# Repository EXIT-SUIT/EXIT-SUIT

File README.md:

# EXIT SUIT
 
The EXIT SUIT is a full-body force-feedback navigation and performance suit for Virtual Reality. This repo contains our code so far for connecting the EXIT SUIT to Unity. 

We are building a community of supporters to help us bring the EXIT SUIT to the public. We recognise it is an important step in the development of human/computer interface and virtual reality.   
<br/><br/> 
   
<br/><br/>
# Community  
 
* Youtube: https://www.youtube.com/@WillieWinkler

* Instagram: https://www.instagram.com/exitsuit/

* Patreon: https://www.patreon.com/EXITSUIT

* Discord: https://discord.gg/Rf7WjFDc

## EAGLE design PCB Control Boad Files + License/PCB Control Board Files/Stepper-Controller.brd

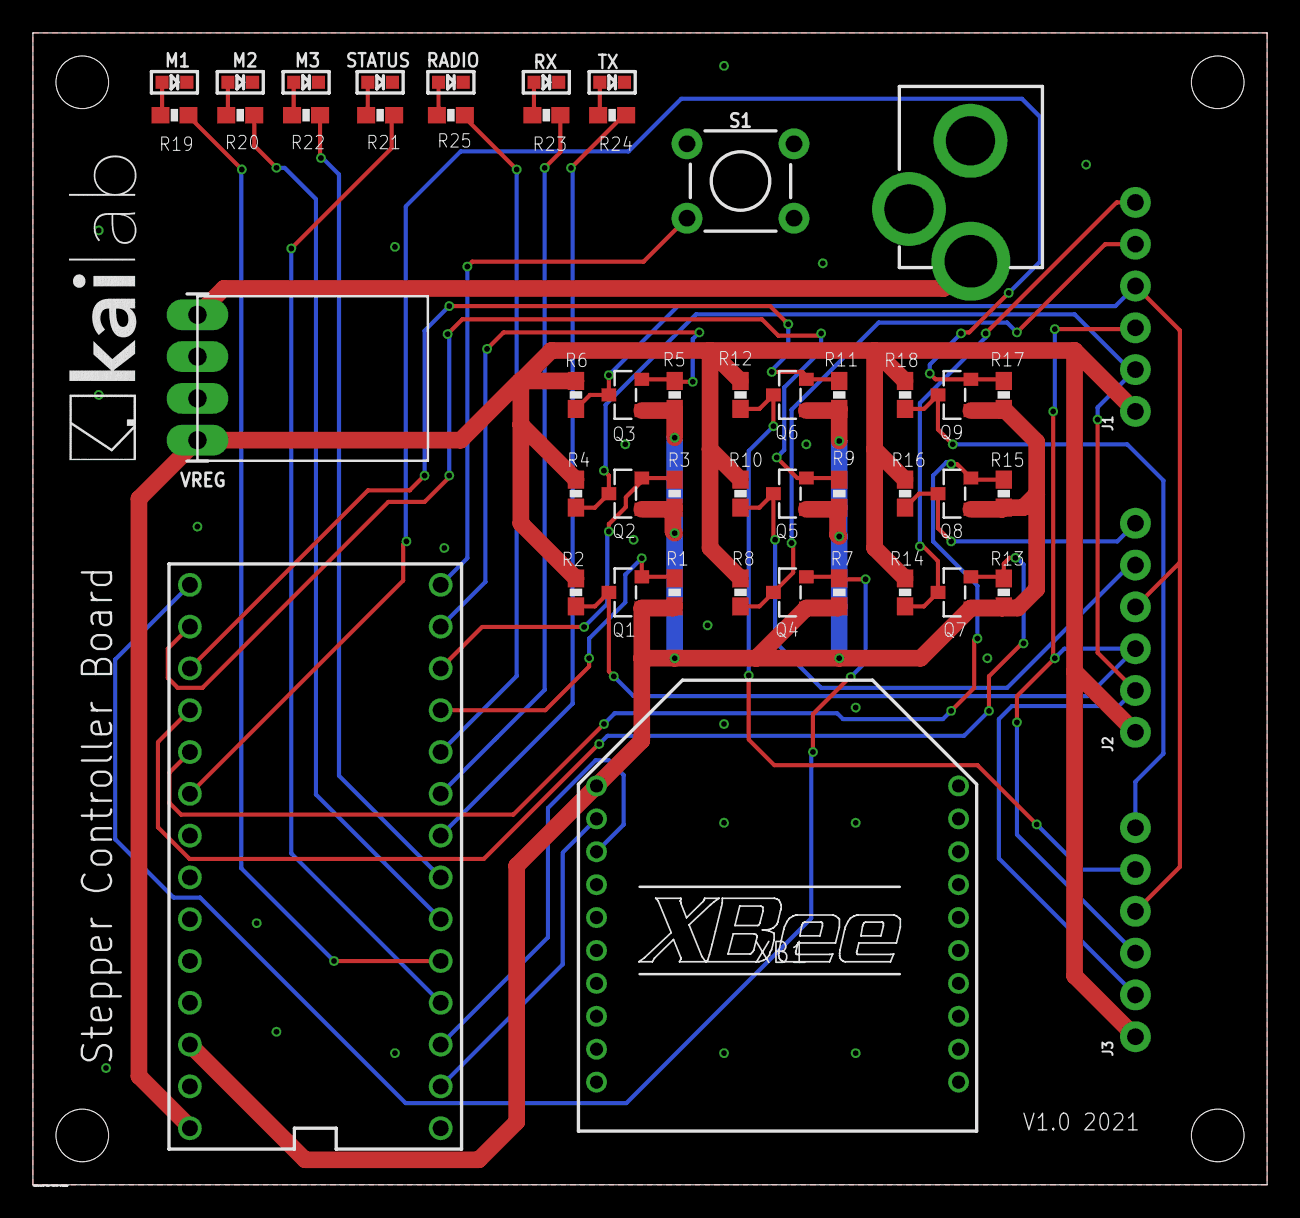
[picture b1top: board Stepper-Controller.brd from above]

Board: 2 copper layers, 75.0 x 70.0 mm, 49 parts (0 on the bottom side), 39 nets.

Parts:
J1, J2, J3: 1X06_NO_SILK
J4: POWER_JACKPTH_LOCK; POWER_JACK_PTH_LOCK
M1, M2, M3: MICROBUILDER_CHIPLED_0603
Q1, Q2, Q3, Q4, Q5, Q6, Q7, Q8, Q9: BSS138; SOT23
R1, R2, R3, R4, R5, R6, R7, R8, R9, R10, R11, R12, R13, R14, R15, R16, R17, R18, R19, R20, R21, R22, R23, R24, R25: CONTROLBOARD_V1.0_SPARKFUN_0603-RES
RADIO: MICROBUILDER_CHIPLED_0603
RX: MICROBUILDER_CHIPLED_0603
S1: MOMENTARY-SWITCH-SPST-PTH-6.0MM; TACTILE_SWITCH_PTH_6.0MM
STATUS: MICROBUILDER_CHIPLED_0603
TX: MICROBUILDER_CHIPLED_0603
U$1: TEENSY_3.1-3.2_DIL; TEENSY_3.0-3.2&LC_DIL
VREG: 1X04_LONGPADS
XB1: XBEE

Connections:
3V3: Q1.1, Q2.1, Q3.1, Q4.1, Q5.1, Q6.1, Q7.1, Q8.1, Q9.1, R1.2, R3.2, R5.2, R7.2, R9.2, R11.2, R13.2, R15.2, R17.2, U$1.3.3V, XB1.1
5V: J1.1, J2.1, J3.1, R2.2, R4.2, R6.2, R8.2, R10.2, R12.2, R14.2, R16.2, R18.2, U$1.VIN, VREG.1
AL1_3V3: Q4.2, R7.1, U$1.13
AL1_5V: J1.5, Q4.3, R8.1
AL2_3V3: Q5.2, R9.1, U$1.14/A0
AL2_5V: J2.5, Q5.3, R10.1
AL3_3V3: Q6.2, R11.1, U$1.15/A1
AL3_5V: J3.5, Q6.3, R12.1
APPON: R21.2, U$1.2
DIR3V3: Q3.2, R5.1, U$1.11
DIR5V: J1.4, J2.4, J3.4, Q3.3, R6.1
EN3V3: Q2.2, R3.1, U$1.10
EN5V: J1.2, J2.2, J3.2, Q2.3, R4.1
GND: J4.GND, J4.GNDBREAK, M1.C, M2.C, M3.C, RADIO.C, RX.C, S1.1, STATUS.C, TX.C, U$1.AGND, U$1.GND, VREG.2, VREG.3, XB1.10
IN+: J4.PWR, VREG.4
unnamed: M1.A, R19.1
unnamed: M2.A, R20.1
unnamed: S1.3, U$1.12
unnamed: R21.1, STATUS.A
unnamed: M3.A, R22.1
unnamed: R23.1, RX.A
unnamed: R24.1, TX.A
unnamed: R25.1, RADIO.A
PEND1_3V3: Q7.2, R13.1, U$1.16/A2
PEND1_5V: J1.6, Q7.3, R14.1
PEND2_3V3: Q8.2, R15.1, U$1.17/A3
PEND2_5V: J2.6, Q8.3, R16.1
PEND3_3V3: Q9.2, R17.1, U$1.18/A4
PEND3_5V: J3.6, Q9.3, R18.1
RX: U$1.0, XB1.2
RX_STATUS: R24.2, U$1.6
STATUS1: R19.2, U$1.3
STATUS2: R20.2, U$1.4
STATUS3: R22.2, U$1.5
STP3V3: Q1.2, R1.1, U$1.9
STP5V: J1.3, J2.3, J3.3, Q1.3, R2.1
TX: U$1.1, XB1.3
TX_STATUS: R23.2, U$1.7
XBEE_STATUS: R25.2, U$1.8

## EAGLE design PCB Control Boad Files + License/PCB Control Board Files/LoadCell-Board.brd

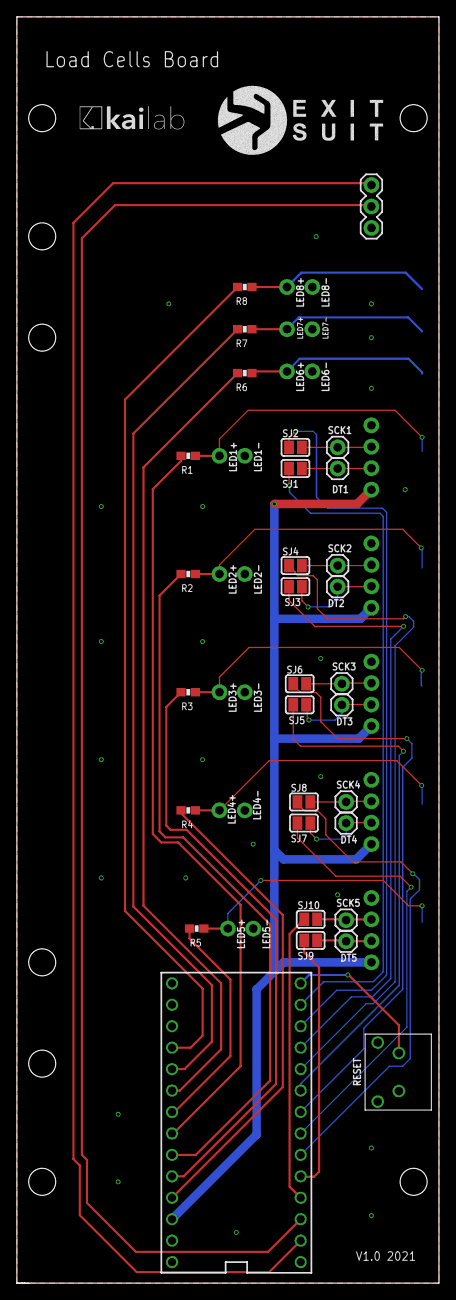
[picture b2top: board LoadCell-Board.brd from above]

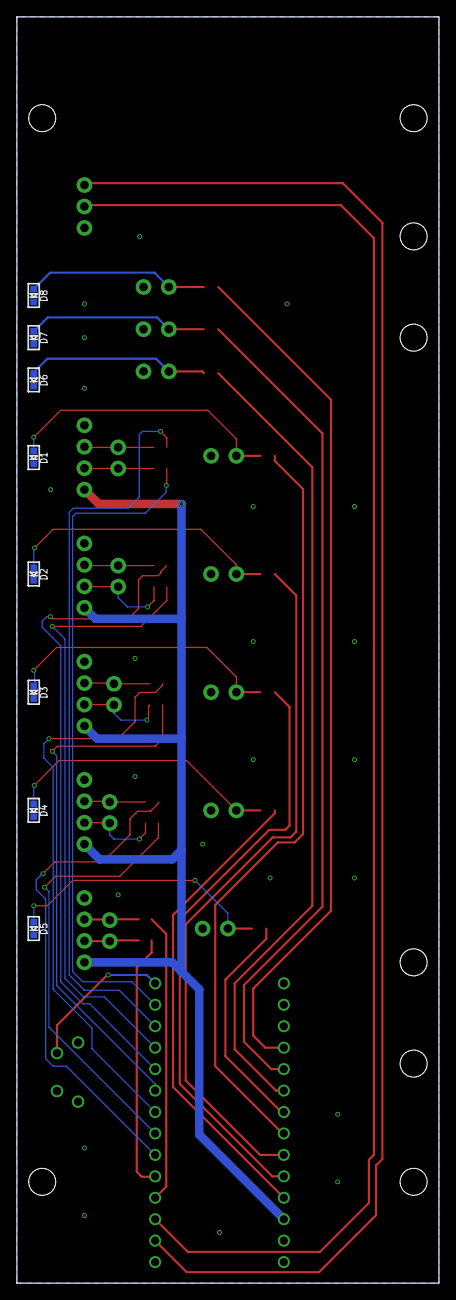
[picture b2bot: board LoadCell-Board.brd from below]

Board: 2 copper layers, 50.0 x 150.0 mm, 60 parts (8 on the bottom side), 41 nets.

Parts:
D1, D2, D3, D4, D5, D6, D7, D8: MICROBUILDER_CHIPLED_0603
DT1, DT2, DT3, DT4, DT5: 1X01
J1, J2, J3, J4, J5: 1X04_NO_SILK
J6: 455-1750-1-ND; 1X03
LED1+, LED1-, LED2+, LED2-, LED3+, LED3-, LED4+, LED4-, LED5+, LED5-, LED6+, LED6-, LED7+, LED7-, LED8+, LED8-: 1X01_NO_SILK
R1, R2, R3, R4, R5, R6, R7, R8: CONTROLBOARD_V1.0_SPARKFUN_0603-RES
RESET: SWITCH; 431256038716
SCK1, SCK2, SCK3, SCK4, SCK5: 1X01
SJ1, SJ2, SJ3, SJ4, SJ5, SJ6, SJ7, SJ8, SJ9, SJ10: MICROBUILDER_SOLDERJUMPER_REFLOW_NOPASTE
U$1: TEENSY_3.1-3.2_DIL; TEENSY_3.0-3.2&LC_DIL

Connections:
3V3: J1.1, J2.1, J3.1, J4.1, J5.1, U$1.3.3V
DT1: SJ1.1, U$1.11
DT2: SJ3.1, U$1.9
DT3: SJ5.1, U$1.7
DT4: SJ7.1, U$1.5
DT5: SJ9.1, U$1.3
GND: D1.C, D2.C, D3.C, D4.C, D5.C, D6.C, D7.C, D8.C, J1.4, J2.4, J3.4, J4.4, J5.4, J6.1, LED1-.1, LED2-.1, LED3-.1, LED4-.1, LED5-.1, LED6-.1, LED7-.1, LED8-.1, RESET.1, RESET.2, RESET.4, U$1.AGND, U$1.GND
LED1: R1.2, U$1.20/A6
LED2: R2.2, U$1.21/A7
LED3: R3.2, U$1.22/A8
LED4: R4.2, U$1.23/A9
LED5: R5.2, U$1.19/A5
LED6: R6.2, U$1.18/A4
LED7: R7.2, U$1.17/A3
LED8: R8.2, U$1.16/A2
unnamed: D1.A, LED1+.1, R1.1
unnamed: DT1.1, J1.2, SJ1.2
unnamed: D2.A, LED2+.1, R2.1
unnamed: J1.3, SCK1.1, SJ2.2
unnamed: D3.A, LED3+.1, R3.1
unnamed: DT2.1, J2.2, SJ3.2
unnamed: RESET.3, U$1.12
unnamed: D4.A, LED4+.1, R4.1
unnamed: J2.3, SCK2.1, SJ4.2
unnamed: D5.A, LED5+.1, R5.1
unnamed: DT3.1, J3.2, SJ5.2
unnamed: D6.A, LED6+.1, R6.1
unnamed: J3.3, SCK3.1, SJ6.2
unnamed: D7.A, LED7+.1, R7.1
unnamed: DT4.1, J4.2, SJ7.2
unnamed: D8.A, LED8+.1, R8.1
unnamed: J4.3, SCK4.1, SJ8.2
unnamed: DT5.1, J5.2, SJ9.2
unnamed: J5.3, SCK5.1, SJ10.2
RX: J6.3, U$1.0
SCK1: SJ2.1, U$1.10
SCK2: SJ4.1, U$1.8
SCK3: SJ6.1, U$1.6
SCK4: SJ8.1, U$1.4
SCK5: SJ10.1, U$1.2
TX: J6.2, U$1.1

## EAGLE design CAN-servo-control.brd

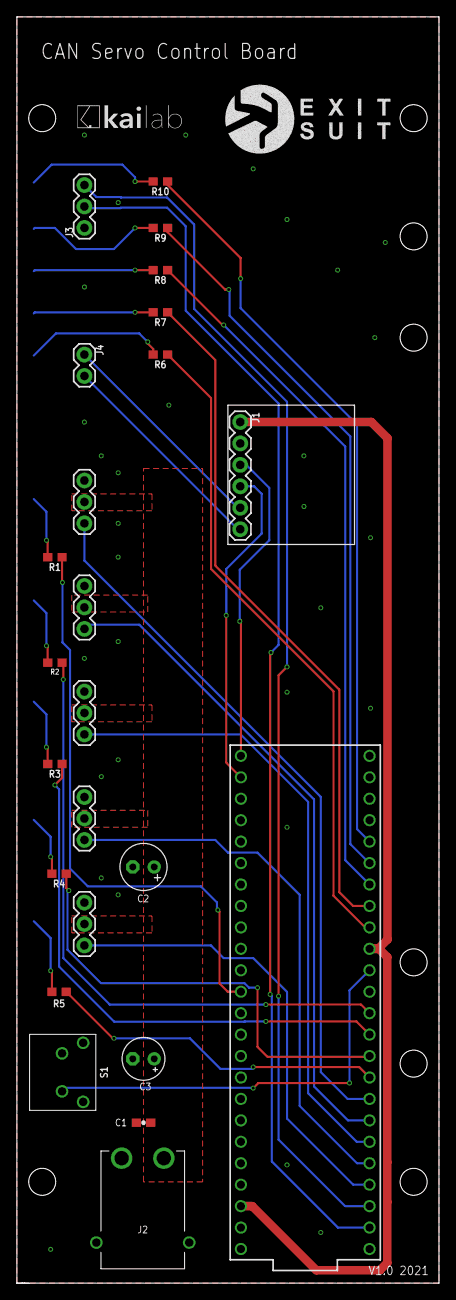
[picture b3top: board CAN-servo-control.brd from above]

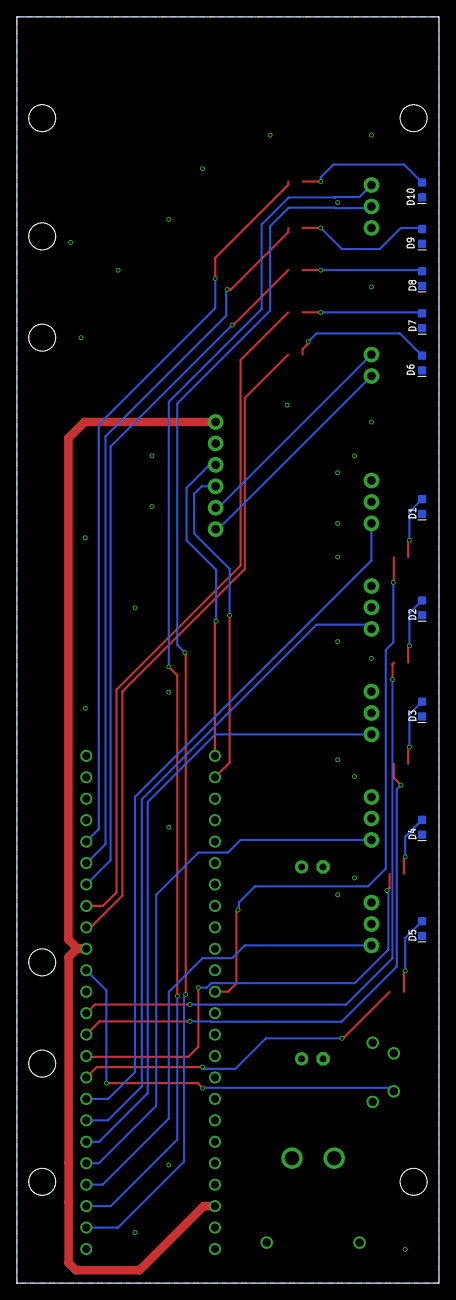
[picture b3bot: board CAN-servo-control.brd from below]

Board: 2 copper layers, 50.0 x 150.0 mm, 34 parts (10 on the bottom side), 35 nets.

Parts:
C1: 0.1uF; SPARKFUN_0603-CAP
C2: 470uF; E2,5-6
C3: 100uF; E2,5-5
D1, D2, D3, D4, D5, D6, D7, D8, D9, D10: SPARKFUN-LED_LED-0603
J1: 1X06
J2: XT30PW-M; XT30PWM
J3: 455-1750-1-ND; 1X03
J4: 1X02
J5: SERVO 5; 1X03
J6: SERVO 4; 1X03
J7: SERVO 3; 1X03
J8: SERVO 2; 1X03
J9: SERVO 1; 1X03
R1, R2, R3, R4, R5, R6, R7, R8, R9, R10: 150; SPARKFUN-RESISTORS_0603
S1: RESET; 431256038716
U$1: TEENSY_3.6_DIL

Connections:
3V3: J1.1, U$1.3.3V, U$1.3.3V3
7V: C1.1, C2.+, C3.+, J2.1, J5.2, J6.2, J7.2, J8.2, J9.2
APPON: R6.1, U$1.24
CANRX: J1.4, U$1.34/A15
CANTX: J1.3, U$1.33/A14
CAN_RX: R9.1, U$1.27
CAN_TX: R10.1, U$1.28
CH: J1.5, J4.1
CL: J1.6, J4.2
DT1: J5.1, U$1.6
DT2: J6.1, U$1.5
DT3: J7.1, U$1.4
DT4: J8.1, U$1.3
DT5: J9.1, U$1.2
GND: C1.2, C2.-, C3.-, D1.C, D2.C, D3.C, D4.C, D5.C, D6.C, D7.C, D8.C, D9.C, D10.C, J1.2, J2.2, J2.3, J2.4, J3.1, J5.3, J6.3, J7.3, J8.3, J9.3, S1.1, S1.2, S1.4, U$1.AGND, U$1.GND, U$1.GND1
MSG_R: R7.1, U$1.25
MSG_S: R8.1, U$1.26
unnamed: S1.3, U$1.12
unnamed: D1.A, R1.2
unnamed: D2.A, R2.2
unnamed: D3.A, R3.2
unnamed: D4.A, R4.2
unnamed: D5.A, R5.2
unnamed: D6.A, R6.2
unnamed: D7.A, R7.2
unnamed: D8.A, R8.2
unnamed: D9.A, R9.2
unnamed: D10.A, R10.2
RX: J3.2, U$1.0
SERVO1: R1.1, U$1.14/A0
SERVO2: R2.1, U$1.10
SERVO3: R3.1, U$1.9
SERVO4: R4.1, U$1.8
SERVO5: R5.1, U$1.7
TX: J3.3, U$1.1

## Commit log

2023-03-24 Readme updated
2023-03-24 Unity Files
2023-03-24 Force Feedback Code
2023-03-24 Other Stuff
2023-03-27 adding git ignores
2023-03-30 Create LICENSE
2023-04-13 Add files via upload
    Files for the EXIT SUIT's first prototype PCB control board
    Can-Servo control with Gerber files
2023-04-13 Add files via upload
    Files for the EXIT SUIT first PCB control board
    Load-cell board and Gerber files
2023-04-13 Add files via upload
    Files for the EXIT SUIT's first PCB control board
    Stepper control and Gerber Files
2023-04-13 PCB Control Board files
    PCB Control Board files
2024-05-01 Create EXIT SUIT PCB control board files
2024-05-01 Create s
2024-05-01 Create test
2024-05-01 Rename license.txt to Blueprints and materials/license.txt
2024-05-01 Moving around files
2024-05-01 Moving PCB Folder
2024-05-01 Moving PCB Files
2024-05-01 Fixing typo
2024-08-28 Delete Blueprints and materials/assembled.dwg
    Updating file with correct layer names

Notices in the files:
parts and their libraries:
SparkFun-Connectors: Licensing: Creative Commons ShareAlike 4.0 International - https://creativecommons.org/licenses/by-sa/4.0
Wurth_Elektronik_Electromechanic_Switch_: Copyright: Würth Elektronik
